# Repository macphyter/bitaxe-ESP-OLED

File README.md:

# bitaxe-ESP-OLED
bitaxe-ESP-OLED is a carrier board for a specific 1.9 inch 170x320 OLED
which is intended to connect to a bitaxe device via the BAP (Bitaxe Accessory Port)
The carrier board contains an ESP32-S3 MCU that drives the display and receives 
status info via UART using the BAP (Bitaxe Accessory Port)

Here is the OLED display

The display attaches to the front of the carrier board using double sided foam tape, and 
the connector wraps around through the notch and attaches to the 30-pin connector on the back.

This OLED display uses a ST7789 controller operates in parallel mode through its 30-pin connector.  
The carrier board uses an ESP32-S3 MCU to drive the OLED.

On the side of the board there is a Reset button, a bootmode button, and two user buttons used for navigating the GUI.

The MCU firmware will display various GUI pages, and the data for these pages will be 
supplied by the bitaxe through the UART.

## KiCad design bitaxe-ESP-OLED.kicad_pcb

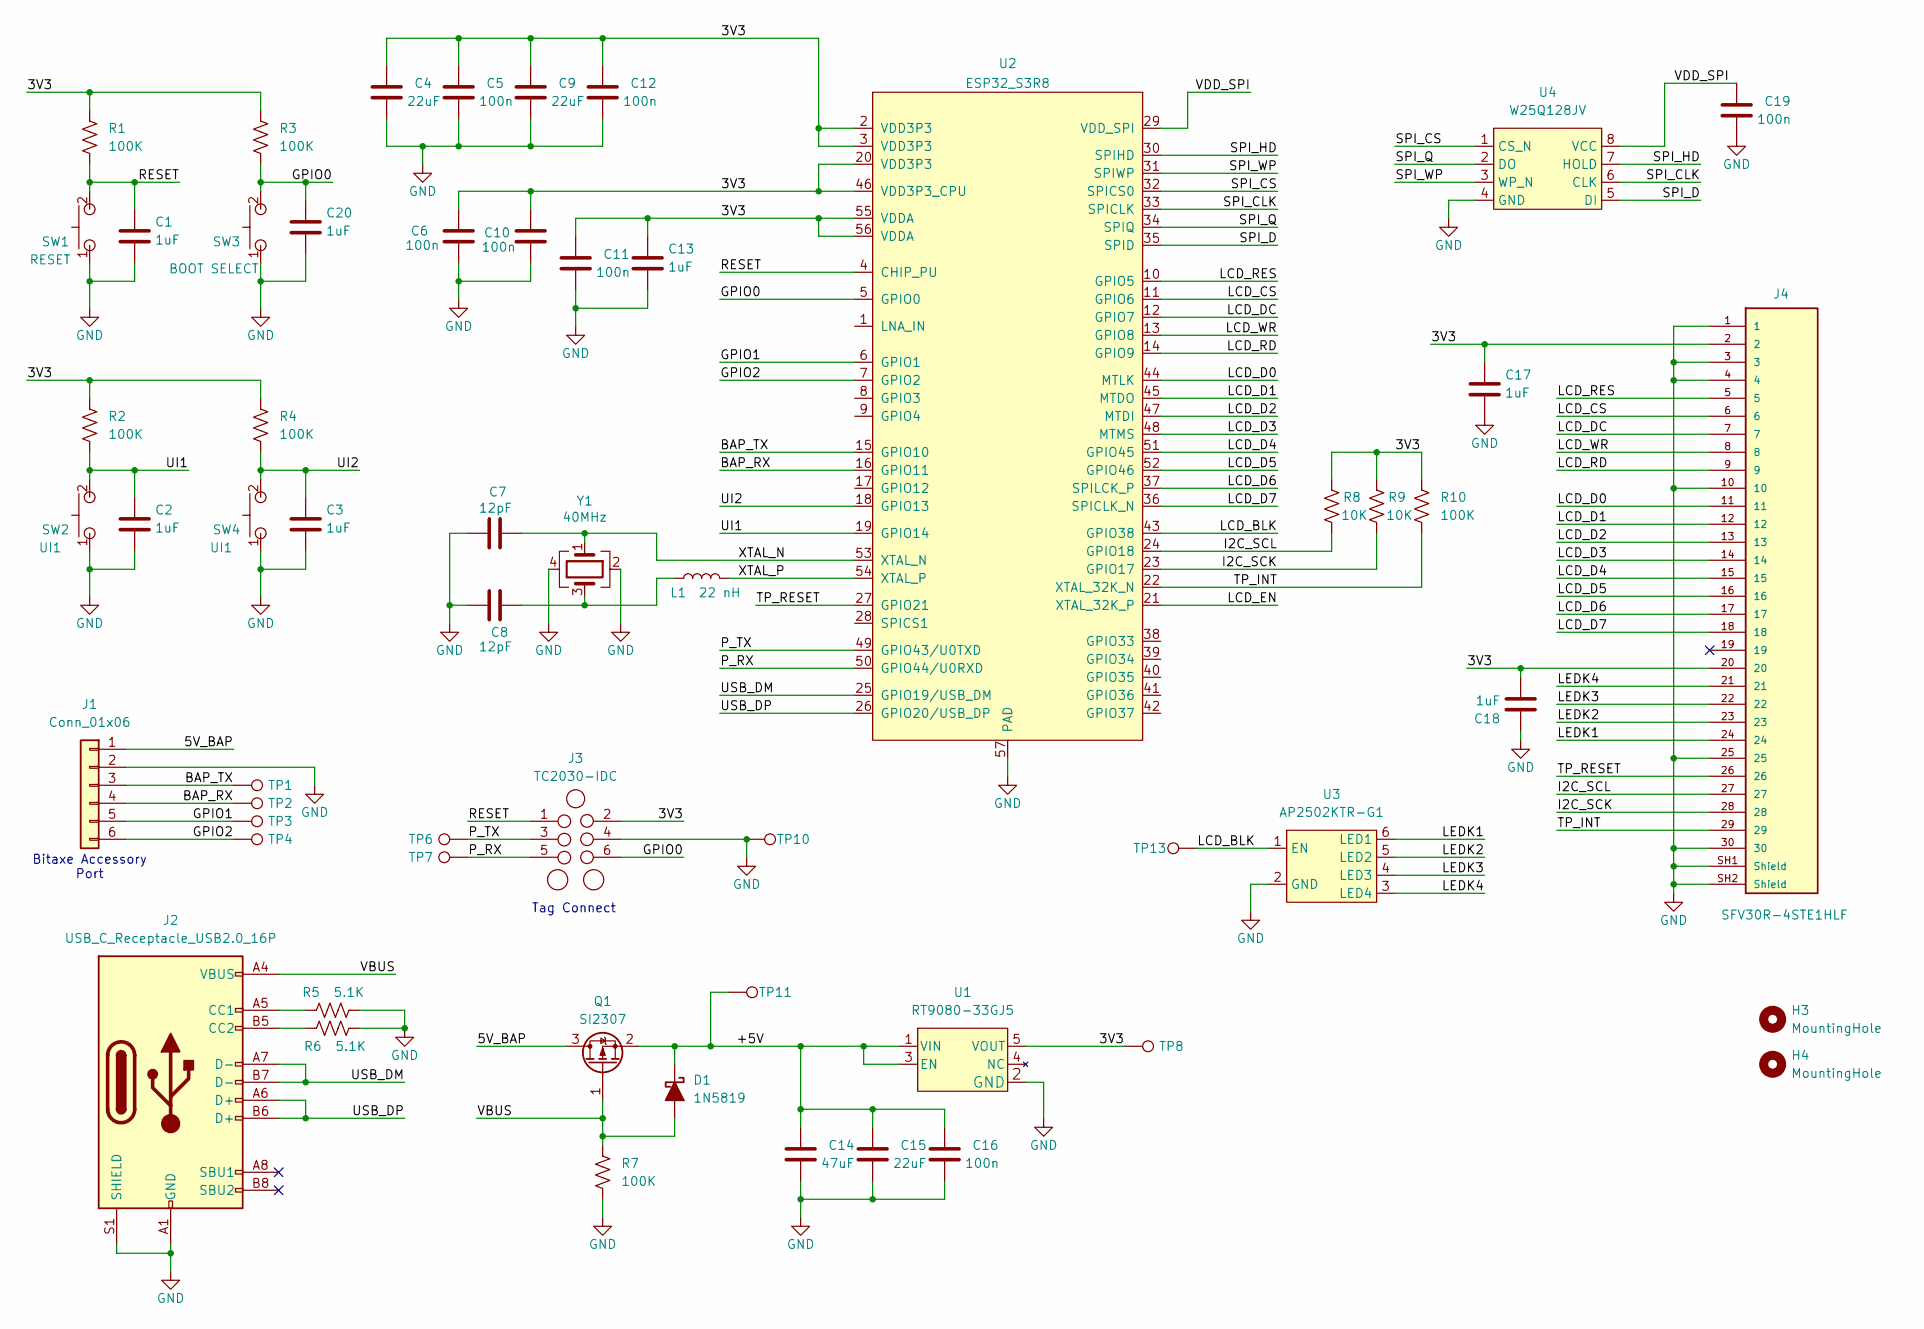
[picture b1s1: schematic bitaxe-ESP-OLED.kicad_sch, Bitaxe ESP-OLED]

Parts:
C1, C18: 1uF; C_0402_1005Metric; PARTNO EMK105BJ105MV-F
C2, C3, C20: 1uF; C_0402_1005Metric; PARTNO TL3340AF160QG
C4, C9, C15: 22uF; C_0805_2012Metric; PARTNO GRM21BC81C226ME44L
C5, C6, C10, C11, C12, C16, C19: 100n; C_0402_1005Metric; PARTNO KGM05AR71C104KH
C7, C8: 12pF; C_0402_1005Metric; PARTNO CC0100JRNPO7BN120
C13, C17: 1uF; C_0402_1005Metric; PARTNO GRM188R60J105KA01D
C14: 47uF; C_1206_3216Metric; PARTNO MSASE31LBB5476MTNA01
D1: 1N5819; D_SOD-123; PARTNO 1N5819W
H3, H4: MountingHole; MountingHole_3mm_Pad_Via
J1: Conn_01x06; PinSocket_2x03_P1.27mm_Vertical_SMD
J2: USB_C_Receptacle_USB2.0_16P; USB_C_Receptacle_GCT_USB4105-xx-A_16P_TopMnt_Horizontal
J3: TC2030-IDC; Tag-Connect_TC2030-IDC-NL_2x03_P1.27mm_Vertical
J4: SFV30R-4STE1HLF; AMPHENOL_SFV30R-4STE1HLF; PARTREV B
L1: 22 nH; L_0603_1608Metric; PARTNO LRC0603CJ22NGV001T
Q1: SI2307; SOT-23-3; PARTNO SI2307CDS-T1-GE3
R1, R2, R3, R4, R7, R10: 100K; R_0402_1005Metric; PARTNO RC0402FR-07100KL
R5, R6: 5.1K; R_0402_1005Metric; PARTNO RC0402FR-135K1L
R8, R9: 10K; R_0402_1005Metric
SW1, SW3: SWITCH-SPST; TL3340-switch; PARTNO TL3340AF160QG
SW2, SW4: SWITCH-SPST; TL3340-switch; PARTNO TL3301NF160QG-KR
TP1, TP2, TP3, TP4, TP6, TP7, TP8, TP10, TP11, TP13: TestPoint; TestPoint_Pad_D1.0mm
U1: RT9080-33GJ5; TSOT-23-5
U2: ESP32_S3R8; QFN-56-1EP_7x7mm_P0.4mm_EP4x4mm_ThermalVias
U3: AP2502KTR-G1; SOT-23-6; PARTNO AP2502KTR-G1
U4: W25Q128JV; WSON-8-1EP_6x5mm_P1.27mm_EP3.4x4.3mm; PARTNO W25Q128JVPIQ
Y1: 40MHz; RH100-oscillator; PARTNO RH100-40.000-12-F-1010-TR

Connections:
/3V3: C4.1, C5.1, C6.1, C9.1, C10.2, C11.1, C12.1, C13.1, C17.1, C18.2, J3.2, J4.2, J4.20, R1.1, R2.1, R3.1, R4.1, R8.1, R9.1, R10.1, TP8.1, U1.5 (VOUT), U2.2 (VDD3P3), U2.3 (VDD3P3), U2.20 (VDD3P3), U2.46 (VDD3P3_CPU), U2.55 (VDDA), U2.56 (VDDA)
/5V_BAP: J1.1, Q1.3 (D)
/+5V: C14.1, C15.1, C16.1, D1.1 (K), Q1.2 (S), TP11.1, U1.1 (VIN), U1.3 (EN)
/BAP_RX: J1.4, TP2.1, U2.16 (GPIO11)
/BAP_TX: J1.3, TP1.1, U2.15 (GPIO10)
/GPIO0: C20.1, J3.6, R3.2, SW3.2, U2.5 (GPIO0)
/GPIO1: J1.5, TP3.1, U2.6 (GPIO1)
/GPIO2: J1.6, TP4.1, U2.7 (GPIO2)
/I2C_SCK: J4.28, R9.2, U2.23 (GPIO17)
/I2C_SCL: J4.27, R8.2, U2.24 (GPIO18)
/LCD_BLK: TP13.1, U2.43 (GPIO38), U3.1 (EN)
/LCD_CS: J4.6, U2.11 (GPIO6)
/LCD_D0: J4.11, U2.44 (MTLK)
/LCD_D1: J4.12, U2.45 (MTDO)
/LCD_D2: J4.13, U2.47 (MTDI)
/LCD_D3: J4.14, U2.48 (MTMS)
/LCD_D4: J4.15, U2.51 (GPIO45)
/LCD_D5: J4.16, U2.52 (GPIO46)
/LCD_D6: J4.17, U2.37 (SPILCK_P)
/LCD_D7: J4.18, U2.36 (SPICLK_N)
/LCD_DC: J4.7, U2.12 (GPIO7)
/LCD_EN: U2.21 (XTAL_32K_P)
/LCD_RD: J4.9, U2.14 (GPIO9)
/LCD_RES: J4.5, U2.10 (GPIO5)
/LCD_WR: J4.8, U2.13 (GPIO8)
/LEDK1: J4.24, U3.6 (LED1)
/LEDK2: J4.23, U3.5 (LED2)
/LEDK3: J4.22, U3.4 (LED3)
/LEDK4: J4.21, U3.3 (LED4)
/P_RX: J3.5, TP7.1, U2.50 (GPIO44/U0RXD)
/P_TX: J3.3, TP6.1, U2.49 (GPIO43/U0TXD)
/RESET: C1.1, J3.1, R1.2, SW1.2, U2.4 (CHIP_PU)
/SPI_CLK: U2.33 (SPICLK), U4.6 (CLK)
/SPI_CS: U2.32 (SPICS0), U4.1 (CS_N)
/SPI_D: U2.35 (SPID), U4.5 (DI)
/SPI_HD: U2.30 (SPIHD), U4.7 (HOLD)
/SPI_Q: U2.34 (SPIQ), U4.2 (DO)
/SPI_WP: U2.31 (SPIWP), U4.3 (WP_N)
/TP_INT: J4.29, R10.2, U2.22 (XTAL_32K_N)
/TP_RESET: J4.26, U2.27 (GPIO21)
/UI1: C2.1, R2.2, SW2.2, U2.19 (GPIO14)
/UI2: C3.1, R4.2, SW4.2, U2.18 (GPIO13)
/USB_DM: J2.A7 (D-), J2.B7 (D-), U2.25 (GPIO19/USB_DM)
/USB_DP: J2.A6 (D+), J2.B6 (D+), U2.26 (GPIO20/USB_DP)
/VBUS: D1.2 (A), J2.A4 (VBUS), J2.A9 (VBUS), J2.B4 (VBUS), J2.B9 (VBUS), Q1.1 (G), R7.1
/VDD_SPI: C19.1, U2.29 (VDD_SPI), U4.8 (VCC)
/XTAL_N: C7.2, U2.53 (XTAL_N), Y1.1
/XTAL_P: L1.2, U2.54 (XTAL_P)
GND: C1.2, C2.2, C3.2, C4.2, C5.2, C6.2, C7.1, C8.1, C9.2, C10.1, C11.2, C12.2, C13.2, C14.2, C15.2, C16.2, C17.2, C18.1, C19.2, C20.2, J1.2, J2.A1 (GND), J2.A12 (GND), J2.B1 (GND), J2.B12 (GND), J2.S1 (SHIELD), J3.4, J4.1, J4.3, J4.4, J4.10, J4.25, J4.30, J4.SH1 (Shield), J4.SH2 (Shield), R5.2, R6.2, R7.2, SW1.1, SW2.1, SW3.1, SW4.1, TP10.1, U1.2 (GND), U2.57 (PAD), U3.2 (GND), U4.4 (GND), Y1.2, Y1.4
unnamed: C8.2, L1.1, Y1.3
unnamed: J2.A5 (CC1), R5.1
unnamed: J2.B5 (CC2), R6.1

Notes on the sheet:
Tag Connect
Bitaxe Accessory Port

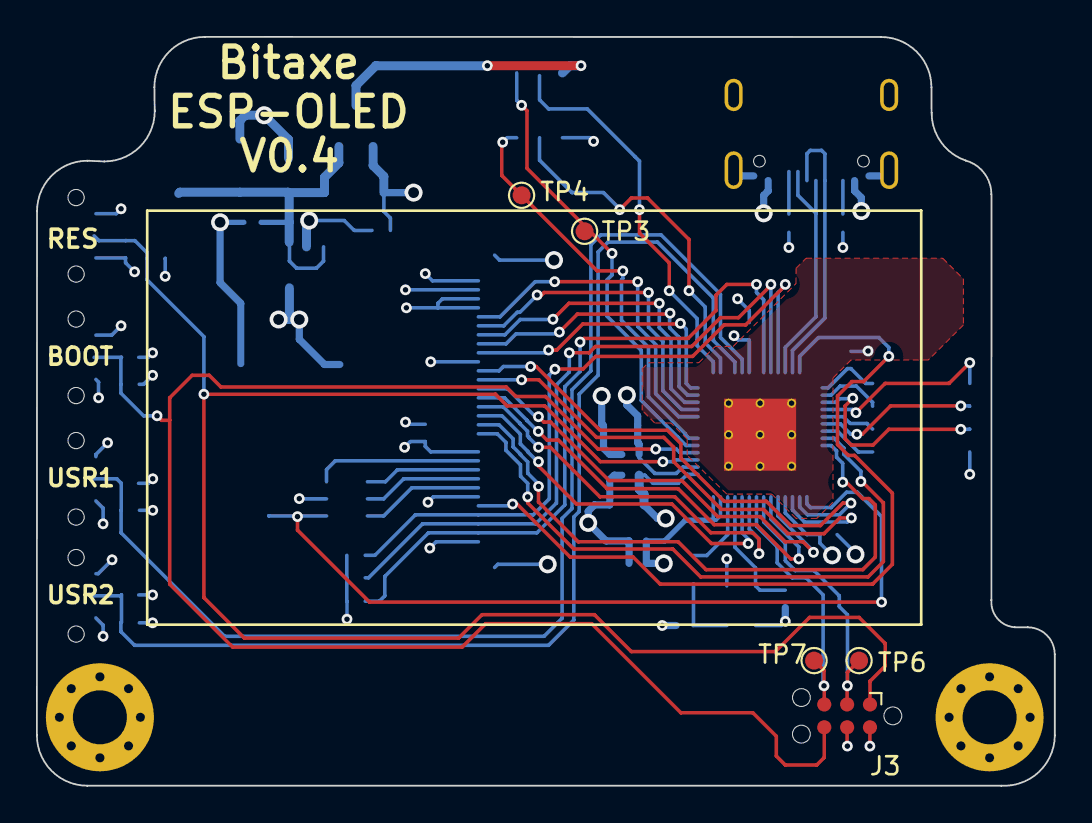
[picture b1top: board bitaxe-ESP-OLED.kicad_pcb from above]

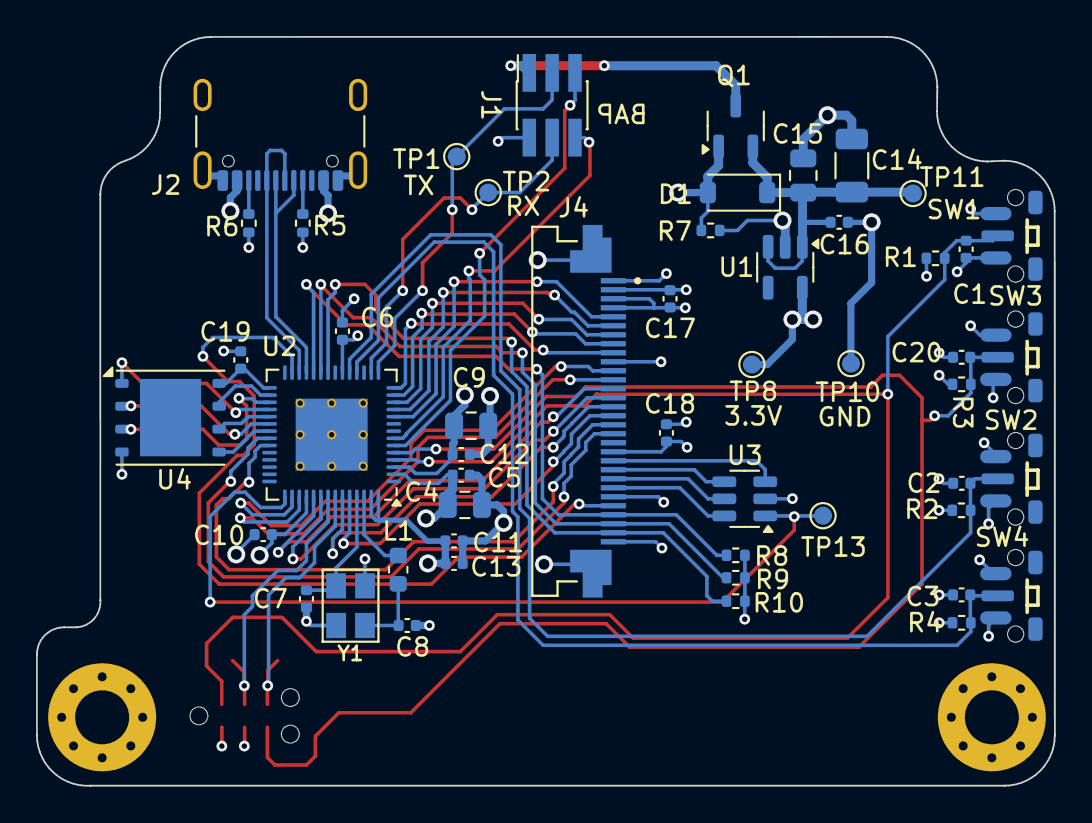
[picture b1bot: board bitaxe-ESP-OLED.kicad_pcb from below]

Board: 4 copper layers, 56.6 x 41.6 mm, 58 parts (51 on the bottom side), 51 nets.

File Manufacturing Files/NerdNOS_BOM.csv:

Reference,Value,Footprint,Qty,DNP,DK,PARTNO
"C1,C2,C3,C13,C17,C18",1uF,Capacitor_SMD:C_0402_1005Metric,6,,-- mixed values --,-- mixed values --
"C4,C9,C15",22uF,Capacitor_SMD:C_0805_2012Metric,3,,490-9956-1-ND,GRM21BC81C226ME44L
"C5,C6,C10,C11,C12,C16,C19",100n,Capacitor_SMD:C_0402_1005Metric,7,,478-KGM05AR71C104KHCT-ND,KGM05AR71C104KH
"C7,C8",12pF,Capacitor_SMD:C_0402_1005Metric,2,,311-3655-1-ND,CC0100JRNPO7BN120
C14,47uF,Capacitor_SMD:C_1206_3216Metric,1,,587-MSASE31LBB5476MTNA01CT-ND,MSASE31LBB5476MTNA01
D1,1N5819,Diode_SMD:D_SOD-123,1,,1655-1N5819WCT-ND,1N5819W
"H1,H2,H3,H4",MountingHole,MountingHole:MountingHole_3.2mm_M3_Pad_Via,4,,,
J1,Conn_01x06,Connector_PinHeader_2.54mm:PinHeader_1x06_P2.54mm_Vertical,1,,,
J2,USB_C_Receptacle_USB2.0_16P,Connector_USB:USB_C_Receptacle_GCT_USB4105-xx-A_16P_TopMnt_Horizontal,1,,,
J3,TC2030-IDC,Connector:Tag-Connect_TC2030-IDC-NL_2x03_P1.27mm_Vertical,1,,,
J4,SFV30R-4STE1HLF,bitaxe:AMPHENOL_SFV30R-4STE1HLF,1,,,
L1,22 nH,Inductor_SMD:L_0603_1608Metric,1,,712-LRC0603CJ22NGV001TCT-ND,  LRC0603CJ22NGV001T
Q1,SI2307,Package_TO_SOT_SMD:SOT-23-3,1,,SI2307CDS-T1-GE3CT-ND,SI2307CDS-T1-GE3
"R1,R2,R3,R4,R7,R10",100K,Resistor_SMD:R_0402_1005Metric,6,,311-100KLRCT-ND,RC0402FR-07100KL
"R5,R6",5.1K,Resistor_SMD:R_0402_1005Metric,2,,13-RC0402FR-135K1LCT-ND,RC0402FR-135K1L
"R8,R9",10K,Resistor_SMD:R_0402_1005Metric,2,,,
"SW1,SW2,SW3,SW4",SWITCH-SPST,-- mixed values --,4,,-- mixed values --,-- mixed values --
"TP1,TP2,TP3,TP4,TP5,TP6,TP7,TP8,TP9,TP10,TP11,TP13",TestPoint,TestPoint:TestPoint_Pad_D1.0mm,12,,,
U1,RT9080-33GJ5,Package_TO_SOT_SMD:TSOT-23-5,1,,,
U2,ESP32_S3R8,bitaxe:QFN-56-1EP_7x7mm_P0.4mm_EP4x4mm_ThermalVias,1,,,
U3,AP2502KTR-G1,Package_TO_SOT_SMD:SOT-23-6,1,,AP2502KTR-G1DICT-ND,AP2502KTR-G1
U4,W25Q128JV,Package_SON:WSON-8-1EP_6x5mm_P1.27mm_EP3.4x4.3mm,1,,W25Q128JVPIQ-ND,W25Q128JVPIQ
Y1,40MHz,bitaxe:RH100-oscillator,1,,2151-RH100-40.000-12-F-1010-TRCT-ND,RH100-40.000-12-F-1010-TR

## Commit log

2024-04-11 commit rendered images
2024-04-13 very rough routing
2024-04-15 main MCU routing to OLED connector
2024-04-16 finish most of the routing
2024-04-16 Finish up routing
2024-04-17 commit version 0.1
2024-05-01 reverse BAP port
2024-05-01 fix outline
2024-05-05 more fpc room
2024-05-05 cleanup
2024-05-18 remove KiCad lock file
2024-05-18 link bitaxe library
2024-05-20 add gitignore file
2024-05-23 moved switches
2024-05-23 tweaks
2024-07-24 v0.3
2024-11-02 Expand copper pour underneath MCU
2025-03-01 update PCB renderings
